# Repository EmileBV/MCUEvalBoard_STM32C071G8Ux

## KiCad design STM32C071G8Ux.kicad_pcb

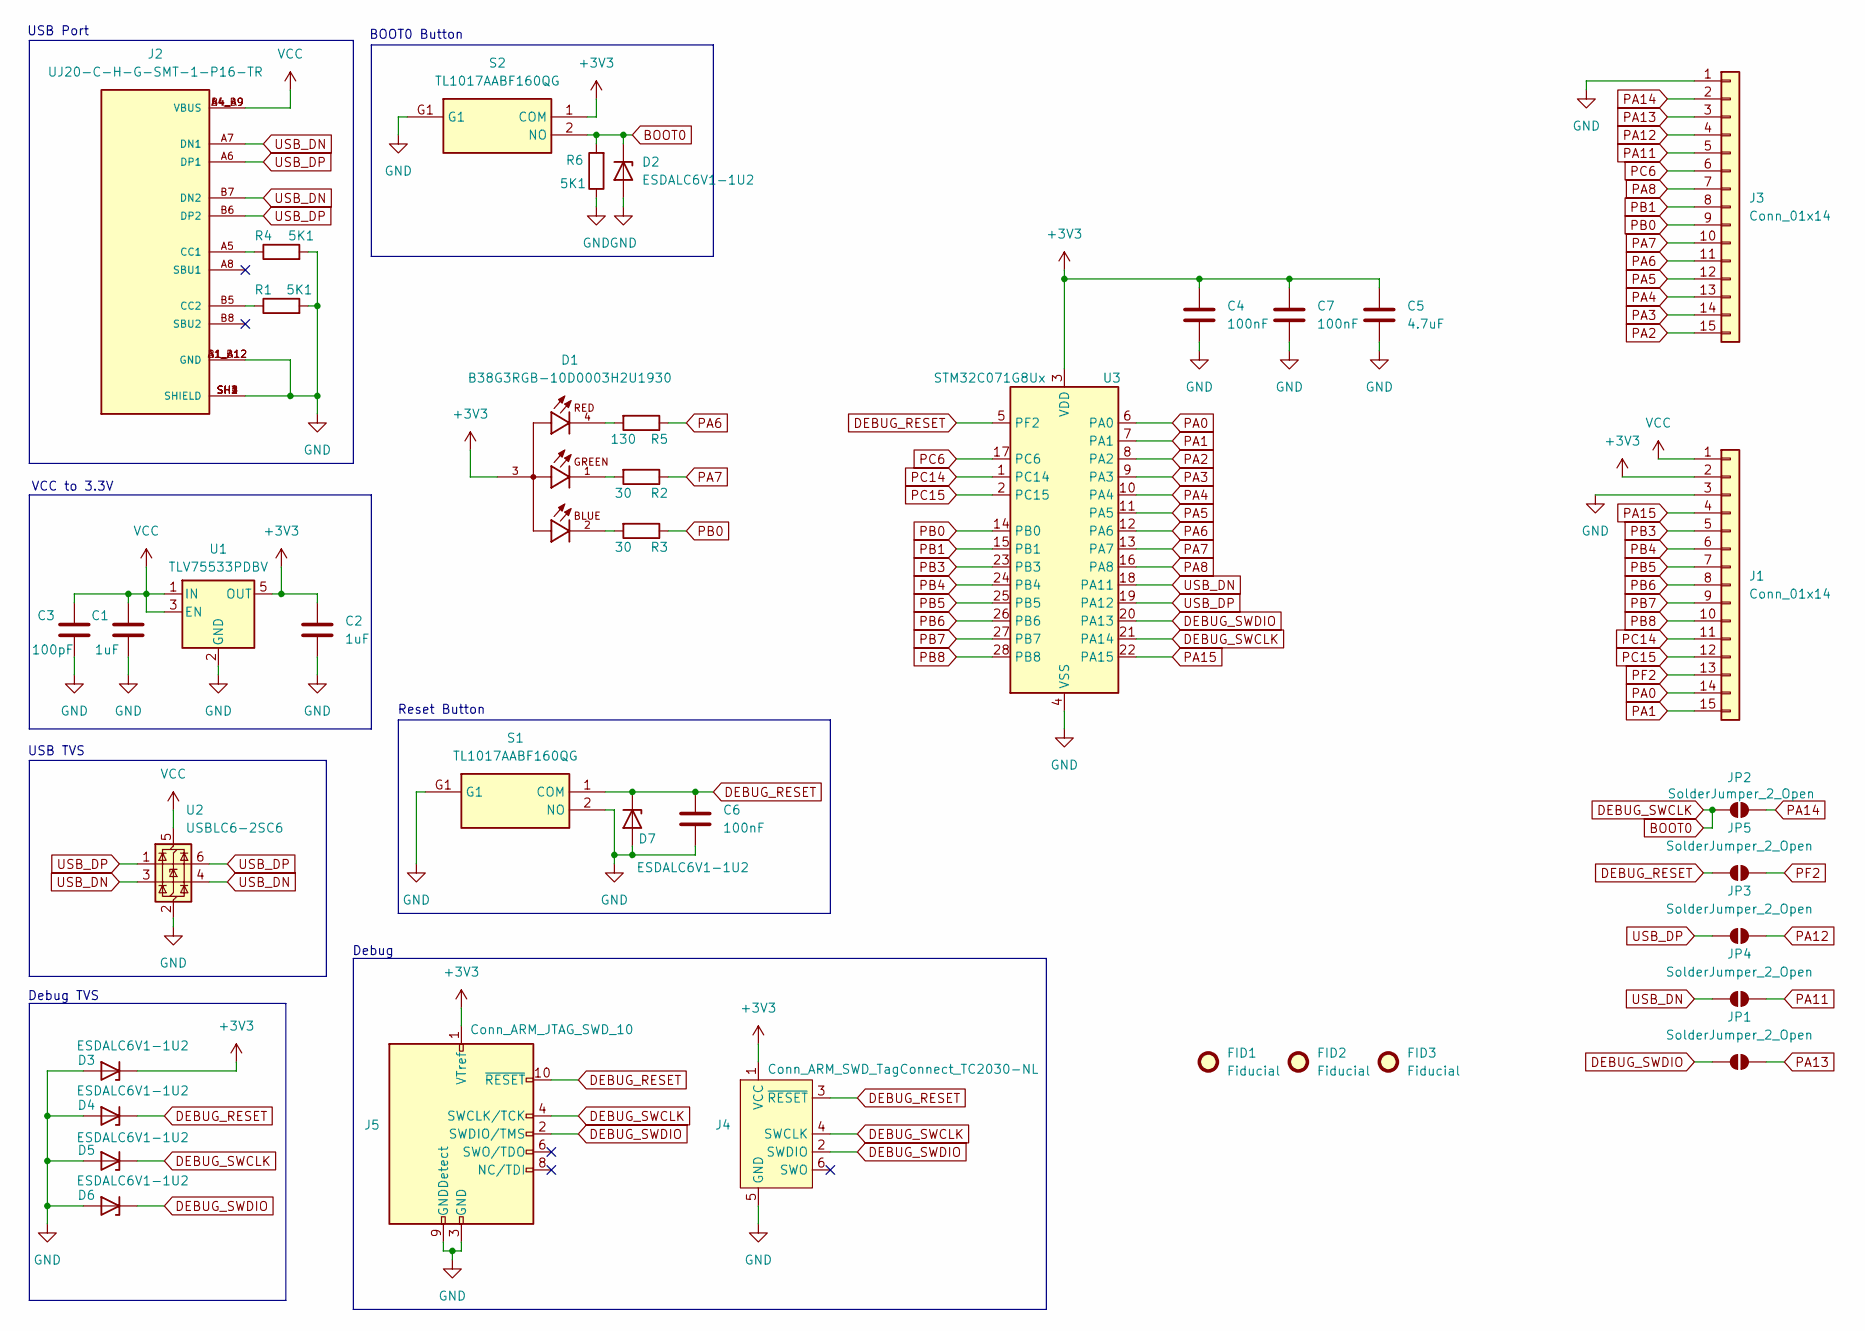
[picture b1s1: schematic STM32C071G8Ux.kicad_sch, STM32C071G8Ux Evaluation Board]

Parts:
C1, C2: 1uF; C_0402_1005Metric
C3: 100pF; C_0402_1005Metric
C4, C6, C7: 100nF; C_0402_1005Metric
C5: 4.7uF; C_0402_1005Metric
D1: B38G3RGB-10D0003H2U1930; LED_B38G3RGB-10D0003H2U1930; PARTREV 1.9; DigiKey_Part_Number 3147-B38G3RGB-10D0003H2U1930TR-ND
D2, D3, D4, D5, D6, D7: ESDALC6V1-1U2; D_0201_0603Metric
FID1, FID2, FID3: Fiducial; Fiducial_0.5mm_Mask1mm
J1, J3: Conn_01x14; PinSocket_1x15_P2.54mm_Vertical
J2: UJ20-C-H-G-SMT-1-P16-TR; SAMESKY_UJ20-C-H-G-SMT-1-P16-TR; PARTREV 1.0; DigiKey_Part_Number 2223-UJ20-C-H-G-SMT-1-P16-TR-ND
J4: Conn_ARM_SWD_TagConnect_TC2030-NL; Tag-Connect_TC2030-IDC-NL_2x03_P1.27mm_Vertical
J5: Conn_ARM_JTAG_SWD_10; PinHeader_2x05_P1.27mm_Vertical_SMD
JP1, JP2, JP3, JP4, JP5: SolderJumper_2_Open; SolderJumper-2_P1.3mm_Open_TrianglePad1.0x1.5mm
R1, R4, R6: 5K1; R_0402_1005Metric
R2, R3: 30; R_0402_1005Metric
R5: 130; R_0402_1005Metric
S1, S2: TL1017AABF160QG; Mouser Part Number 612-TL1017AABF160QG
U1: TLV75533PDBV; SOT-23-5
U2: USBLC6-2SC6; SOT-23-6
U3: STM32C071G8Ux; QFN-28_4x4mm_P0.5mm

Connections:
+3V3: C2.1, C4.1, C5.1, C7.1, D1.3, D3.1 (K), J1.2, J4.1 (VCC), J5.1 (VTref), S2.1 (COM), U1.5 (OUT), U3.3 (VDD)
BOOT0: D2.1 (K), D5.1 (K), J4.4 (SWCLK), J5.4 (SWCLK/TCK), JP2.1 (A), R6.2, S2.2 (NO), U3.21 (PA14)
DEBUG_RESET: C6.1, D4.1 (K), D7.1 (K), J4.3 (~RESET), J5.10 (~RESET), JP5.1 (A), S1.1 (COM), U3.5 (PF2)
DEBUG_SWDIO: D6.1 (K), J4.2 (SWDIO), J5.2 (SWDIO/TMS), JP1.1 (A), U3.20 (PA13)
GND: C1.2, C2.2, C3.2, C4.2, C5.2, C6.2, C7.2, D2.2 (A), D3.2 (A), D4.2 (A), D5.2 (A), D6.2 (A), D7.2 (A), J1.3, J2.A1_B12 (GND), J2.B1_A12 (GND), J2.SH1 (SHIELD), J2.SH2 (SHIELD), J2.SH3 (SHIELD), J2.SH4 (SHIELD), J3.1, J4.5 (GND), J5.3 (GND), J5.5 (GND), J5.9 (GNDDetect), R1.2, R4.2, R6.1, S1.2 (NO), S1.G1, S2.G1, U1.2 (GND), U2.2 (GND), U3.4 (VSS)
unnamed: D1.1, R2.2
unnamed: D1.2, R3.2
unnamed: D1.4, R5.2
unnamed: J2.A5 (CC1), R4.1
unnamed: J2.B5 (CC2), R1.1
PA0: J1.14, U3.6 (PA0)
PA1: J1.15, U3.7 (PA1)
PA2: J3.15, U3.8 (PA2)
PA3: J3.14, U3.9 (PA3)
PA4: J3.13, U3.10 (PA4)
PA5: J3.12, U3.11 (PA5)
PA6: J3.11, R5.1, U3.12 (PA6)
PA7: J3.10, R2.1, U3.13 (PA7)
PA8: J3.7, U3.16 (PA8)
PA11: J3.5, JP4.2 (B)
PA12: J3.4, JP3.2 (B)
PA13: J3.3, JP1.2 (B)
PA14: J3.2, JP2.2 (B)
PA15: J1.4, U3.22 (PA15)
PB0: J3.9, R3.1, U3.14 (PB0)
PB1: J3.8, U3.15 (PB1)
PB3: J1.5, U3.23 (PB3)
PB4: J1.6, U3.24 (PB4)
PB5: J1.7, U3.25 (PB5)
PB6: J1.8, U3.26 (PB6)
PB7: J1.9, U3.27 (PB7)
PB8: J1.10, U3.28 (PB8)
PC6: J3.6, U3.17 (PC6)
PC14: J1.11, U3.1 (PC14)
PC15: J1.12, U3.2 (PC15)
PF2: J1.13, JP5.2 (B)
USB_DN: J2.A7 (DN1), J2.B7 (DN2), JP4.1 (A), U2.3 (I/O2), U2.4 (I/O2), U3.18 (PA11)
USB_DP: J2.A6 (DP1), J2.B6 (DP2), JP3.1 (A), U2.1 (I/O1), U2.6 (I/O1), U3.19 (PA12)
VCC: C1.1, C3.1, J1.1, J2.A4_B9 (VBUS), J2.B4_A9 (VBUS), U1.1 (IN), U1.3 (EN), U2.5 (VBUS)

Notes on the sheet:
Reset Button
VCC to 3.3V
Debug
BOOT0 Button
USB TVS
Debug TVS
USB Port

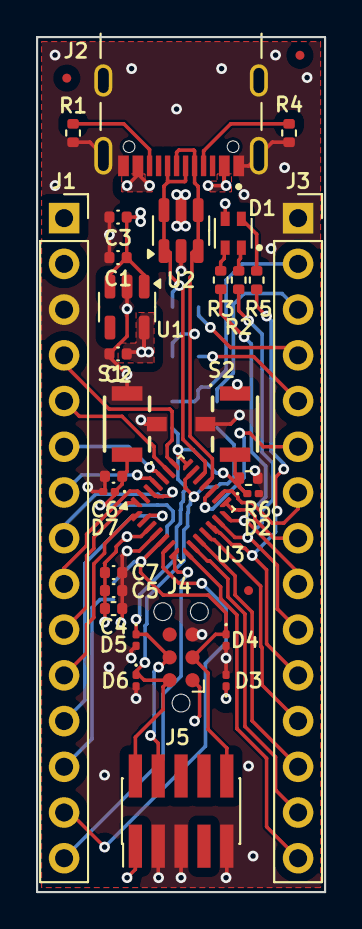
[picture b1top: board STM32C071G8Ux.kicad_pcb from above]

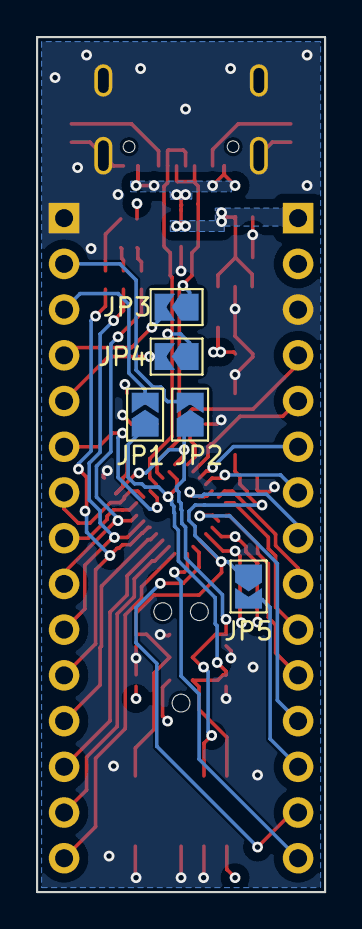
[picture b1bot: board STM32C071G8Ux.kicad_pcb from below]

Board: 4 copper layers, 16.0 x 47.5 mm, 38 parts (5 on the bottom side), 39 nets.

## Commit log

2025-04-16 routing done but drc errors
2025-04-17 fixed some design rules
